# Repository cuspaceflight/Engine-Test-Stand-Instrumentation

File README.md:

# Cambridge University Space Flight Engine Test Stand

This repo contains documents for CUSF engine test stand. The electronics are split across 2 circuit boards:

**Servo + Solenoid Board**  Drives 2 solenoid valves (MPQ6610 half-bridge ICs) and up to 4 servos
**Instrumentation Board** Reads pressure transducers, thermocouples, and a load cell for thrust measurement

A laptop running ground-station software sends commands to the ESP32 on the servo board, and polls the Instrumentation Board to read sensor data

## Board Details

### Servo + Solenoid Board

This board contains the circuits for driving the servos and solenoids. Uses an ESP32 microcontroller (ESP32 S3 DevKit C1). The microcontroller is alos responsible for: 
 - Communication with laptop
 - Driving servos and solenoids
 - Inputs raw data from sensors and sends to laptop

#### Solenoid Section

Each of the solenoid channels uses an **MPS MPQ6610** half-bridge power driver. 

#### Servo Section

4 servos (FeeTech 180 Degrees Digital Servo 7.4V 35kg/cm FT5330M)
 - PWM signal from ESP32

### Instrumentation Board

- Load cell
- 8 Pressure sensors
- 4 thermocouples

## Repository Structure

```
cusf-engine_test_stand/
│
├── hardware/
│   ├── master-board/
│   │   ├── kicad/              # Schematic + PCB project
│   │
│   ├── servo-solenoid-board/
│   │   ├── kicad/
│   │
│   ├── instrumentation-board/
│   │   ├── kicad/
│   │
│   ├── Datasheets
│   │   ├── MPQ6610.pdf
│   │
│
├── Software/
│   ├── servo/
│   ├── solenoid/
│   ├── instrumentation/
│   ├──Laptop software (GUI + logging)
│
└── README.md

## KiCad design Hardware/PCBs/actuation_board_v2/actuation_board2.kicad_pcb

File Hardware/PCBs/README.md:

# CUSF Load Cell Interface Board

## Overview

Signal conditioning board for the PW16A load cell, providing excitation voltage, instrumentation amplification, low-pass filtering, and buffered voltage references for ADC reading.

---

## Connector

| Designator | Description |
|------------|-------------|
| J1 | RS Pro M12 Connector Female, 8W-8C, 5m, PVC, Shield |

---

## Load Cell

| Parameter | Value |
|-----------|-------|
| Model | PW16A |
| Sensitivity | 2 mV/V |
| Excitation Voltage | 10 V |
| Full-scale Output | 20 mV (0.02 V) |

---

## Power Section

### Voltage Regulation & References

| Designator | Part | Description | Package |
|------------|------|-------------|---------|
| U4 | L78L05 | 5V Positive Linear Regulator, 100mA, 30V Max Input | SOIC-8 |
| U2 | REF5010AD | 10V Precision Voltage Reference, 0.1% Accuracy, 10mA, Low Noise | SOIC-8 |
| U5 | REF3033 | 3.3V CMOS Voltage Reference, 50 ppm/°C Max, 50 µA | SOT-23 |

### Op-Amp Buffers

| Designator | Part | Description | Package | Purpose |
|------------|------|-------------|---------|---------|
| U3 | OPA197xD | 36V Precision, Rail-to-Rail I/O, Low Offset Voltage Op-Amp | SOIC-8 | 10V reference buffer |
| U6 | OPA333xxD | 1.8V microPower, CMOS Zero-Drift Op-Amp | SOIC-8 | 3.3V reference buffer |

### Resistors

| Designator | Value | Package |
|------------|-------|---------|
| R2 | 1 Ω | 0805 |
| R3 | 16.2 kΩ | 0805 |
| R4 | 1.8 kΩ | 0805 |

### Capacitors

| Designator | Value | Package |
|------------|-------|---------|
| C3 | 100 nF | 0805 |
| C4 | 100 nF | 0805 |
| C5 | 100 nF | 0805 |
| C6 | 100 nF | 0805 |
| C7 | 10 µF | 0805 |
| C8 | 10 µF | 0805 |
| C9 | 10 µF | 0805 |
| C10 | 1 µF | 0805 |
| C11 | 100 nF | 0805 |
| C12 | 1 µF | 0805 |
| C13 | 100 nF | 0805 |

### Outputs

| Signal | Source | Description |
|--------|--------|-------------|
| VOUT_10V | REF5010AD + OPA197xD buffer | 10V excitation for load cell |
| VREF_0.33V | REF3033 + OPA333xxD buffer | 0.33V reference for ADC |

---

## Analogue Signal Section

### Instrumentation Amplifier

| Designator | Part | Description | Package |
|------------|------|-------------|---------|
| U1 | AD8422 | Single High Performance, Low Power, Rail-to-Rail Precision In-Amp | SOIC-8 |

| Parameter | Value |
|-----------|-------|
| Gain (G) | 150 |
| Gain Resistor (RG) | 133 Ω |
| Formula | RG = 19.8 kΩ / (G − 1) |
| Supply Voltage | +15V (single-supply) |
| Output to ESP | 3.0 V |

### Gain Resistor

| Designator | Value | Package |
|------------|-------|---------|
| RG | 133 Ω | 0805 |

### Low-Pass Filter

| Designator | Value | Package | Notes |
|------------|-------|---------|-------|
| R1 | 5.36 kΩ | 0805 | Series resistor |
| C1 | 10 nF | 0805 | Shunt capacitor |

| Parameter | Value |
|-----------|-------|
| Cut-off Frequency | 2.97 kHz |
| Topology | RC low-pass filter |

### Decoupling Capacitor

| Designator | Value | Package |
|------------|-------|---------|
| C2 | 0.1 µF | 0805 |

### Signals

| Signal | Direction | Description |
|--------|-----------|-------------|
| LC_SIG+ | Input | Load cell differential signal (+) |
| LC_SIG- | Input | Load cell differential signal (−) |
| +15V_Analog | Input | 15V supply for AD8422 |
| V_REF | Input | 0.33V reference for AD8422 output offset |
| ADC_OUT_TO_MIC | Output | Filtered, amplified signal to microcontroller ADC |
| AGND | — | Analogue ground |

---

## Inter-Sheet Connections

| Main Sheet Label | Power Sheet | Analogue Signal Sheet | J1 (M12 Connector) |
|------------------|-------------|----------------------|---------------------|
| VIN_15V | Input | — | — |
| VOUT_10V | ← Output | — | — |
| VREF_0.33V | ← Output | → V_REF | — |
| +10V_EXC | — | — | Pins 1, 8 |
| LC_SIG+ | — | ← Input | Pin (signal) |
| LC_SIG- | — | ← Input | Pin (signal) |
| AGND | ✓ | ✓ | Ground pins |
| ADC_OUT_TO_MIC | — | → Output | — |

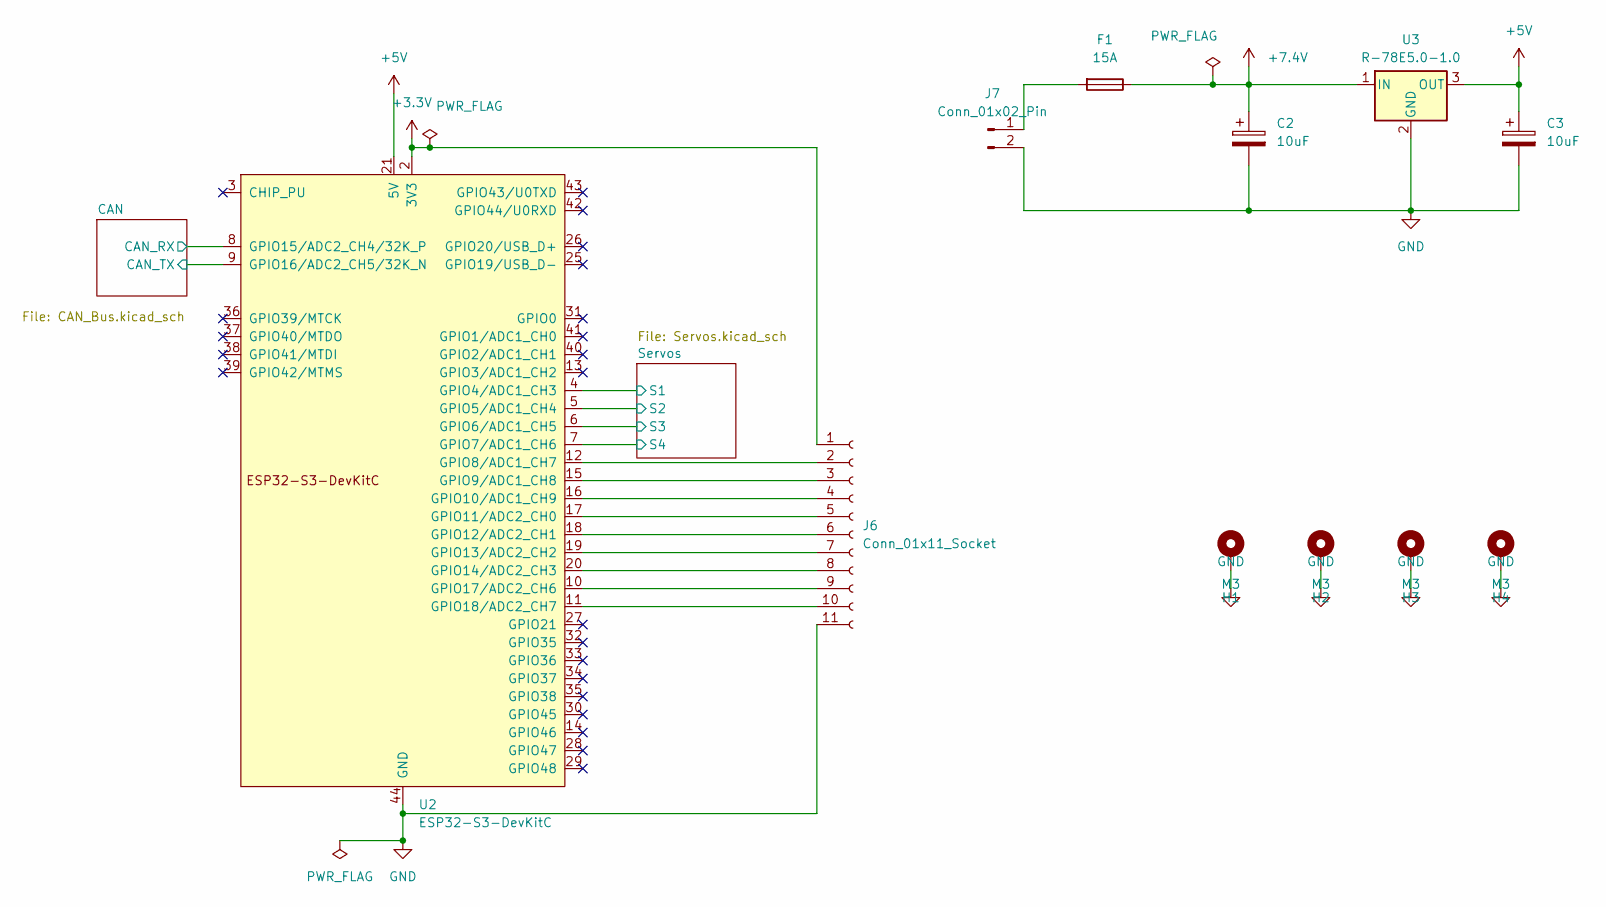
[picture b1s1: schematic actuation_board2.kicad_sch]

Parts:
C2, C3: 10uF; C_0603_1608Metric_Pad1.08x0.95mm_HandSolder
F1: 15A; Fuse_1206_3216Metric_Pad1.42x1.75mm_HandSolder
H1, H2, H3, H4: M3; MountingHole_3.2mm_M3_Pad_Via
J6: Conn_01x11_Socket; PinSocket_1x11_P2.54mm_Vertical
J7: Conn_01x02_Pin; AMASS_XT60PW-M_1x02_P7.20mm_Horizontal
U2: ESP32-S3-DevKitC
U3: R-78E5.0-1.0; Converter_DCDC_RECOM_R-78E-0.5_THT

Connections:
+3.3V: J6.1, U2.1 (3V3), U2.2 (3V3); also elsewhere on the board
+5V: C3.1, U2.21 (5V), U3.3 (OUT)
+7.4V: C2.1, F1.1, U3.1 (IN); also elsewhere on the board
/CAN/CAN_RX: U2.8 (GPIO15/ADC2_CH4/32K_P); also elsewhere on the board
/CAN/CAN_TX: U2.9 (GPIO16/ADC2_CH5/32K_N); also elsewhere on the board
/Servos/S1: U2.4 (GPIO4/ADC1_CH3); also elsewhere on the board
/Servos/S2: U2.5 (GPIO5/ADC1_CH4); also elsewhere on the board
/Servos/S3: U2.6 (GPIO6/ADC1_CH5); also elsewhere on the board
/Servos/S4: U2.7 (GPIO7/ADC1_CH6); also elsewhere on the board
GND: C2.2, C3.2, H1.1, H2.1, H3.1, H4.1, J6.11, J7.2, U2.22 (GND), U2.23 (GND), U2.24 (GND), U2.44 (GND), U3.2 (GND); also elsewhere on the board
unnamed: J6.2, U2.12 (GPIO8/ADC1_CH7)
unnamed: J6.3, U2.15 (GPIO9/ADC1_CH8)
unnamed: J6.4, U2.16 (GPIO10/ADC1_CH9)
unnamed: J6.5, U2.17 (GPIO11/ADC2_CH0)
unnamed: J6.6, U2.18 (GPIO12/ADC2_CH1)
unnamed: J6.7, U2.19 (GPIO13/ADC2_CH2)
unnamed: J6.8, U2.20 (GPIO14/ADC2_CH3)
unnamed: J6.9, U2.10 (GPIO17/ADC2_CH6)
unnamed: J6.10, U2.11 (GPIO18/ADC2_CH7)
unnamed: F1.2, J7.1

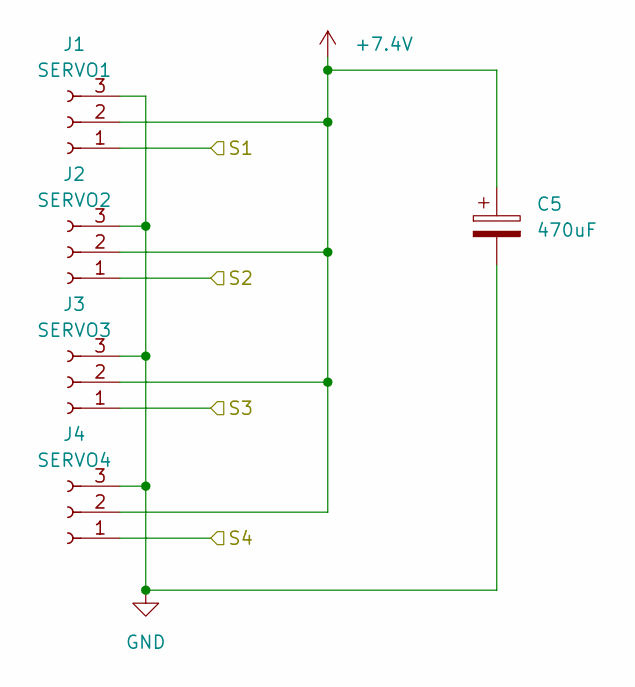
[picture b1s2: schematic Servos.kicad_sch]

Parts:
C5: 470uF; CP_Radial_D10.0mm_P7.50mm
J1: SERVO1; PinHeader_1x03_P2.54mm_Vertical
J2: SERVO2; PinHeader_1x03_P2.54mm_Vertical
J3: SERVO3; PinHeader_1x03_P2.54mm_Vertical
J4: SERVO4; PinHeader_1x03_P2.54mm_Vertical

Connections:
+7.4V: C5.1, J1.2, J2.2, J3.2, J4.2; also elsewhere on the board
/Servos/S1: J1.1; also elsewhere on the board
/Servos/S2: J2.1; also elsewhere on the board
/Servos/S3: J3.1; also elsewhere on the board
/Servos/S4: J4.1; also elsewhere on the board
GND: C5.2, J1.3, J2.3, J3.3, J4.3; also elsewhere on the board

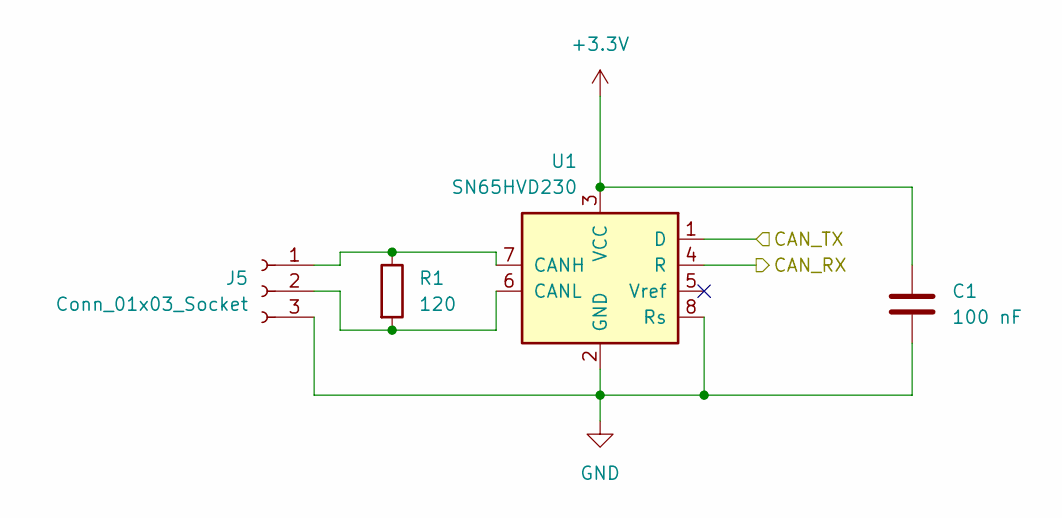
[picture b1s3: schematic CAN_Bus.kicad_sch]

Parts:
C1: 100 nF; C_0603_1608Metric_Pad1.08x0.95mm_HandSolder
J5: Conn_01x03_Socket; PinSocket_1x03_P2.54mm_Vertical
R1: 120; R_0805_2012Metric_Pad1.20x1.40mm_HandSolder
U1: SN65HVD230; SOIC-8_3.9x4.9mm_P1.27mm

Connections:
+3.3V: C1.1, U1.3 (VCC); also elsewhere on the board
/CAN/CAN_RX: U1.4 (R); also elsewhere on the board
/CAN/CAN_TX: U1.1 (D); also elsewhere on the board
GND: C1.2, J5.3, U1.2 (GND), U1.8 (Rs); also elsewhere on the board
unnamed: J5.1, R1.1, U1.7 (CANH)
unnamed: J5.2, R1.2, U1.6 (CANL)

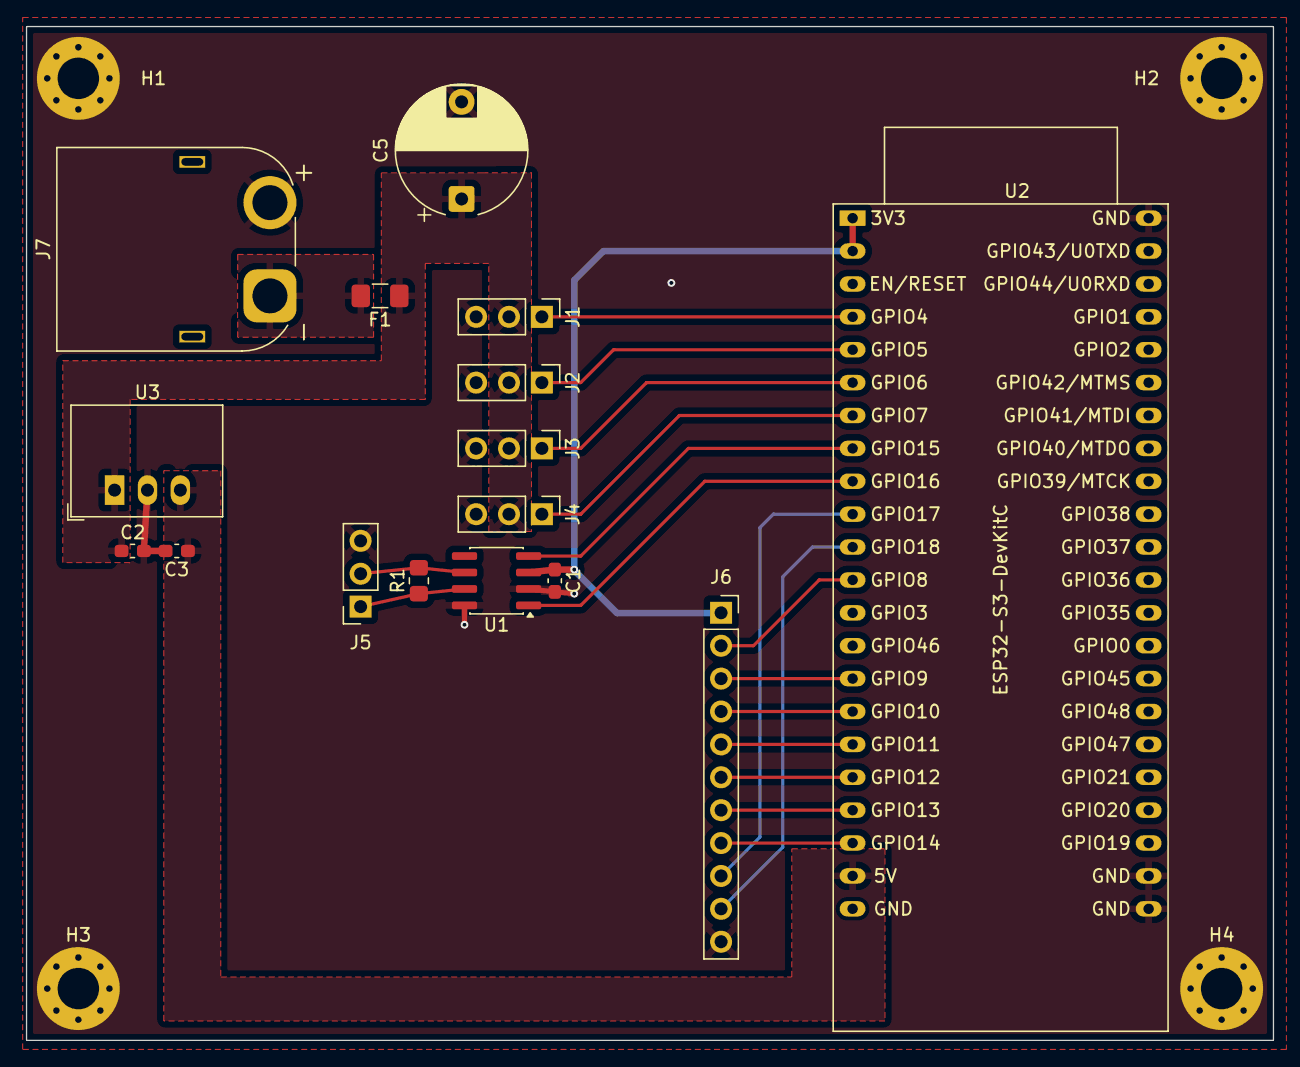
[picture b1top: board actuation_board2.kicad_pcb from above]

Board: 2 copper layers, 96.3 x 78.3 mm, 20 parts (0 on the bottom side), 22 nets.

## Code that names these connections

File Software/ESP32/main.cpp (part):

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    // PWM generator. We configure 4 channels at 50Hz with 14-bit
    // resolution, then attach each to its GPIO pin.
    //
    // Channel 0 → GPIO10 → Servo 1
    // Channel 1 → GPIO11 → Servo 2
    // Channel 2 → GPIO12 → Servo 3
    // Channel 3 → GPIO13 → Servo 4

    int servo_pins[4] = {PIN_SERVO1, PIN_SERVO2, PIN_SERVO3, PIN_SERVO4};

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
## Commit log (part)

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2026-03-08 Add README for CUSF Test Stand actuation board
    Added detailed documentation for the CUSF Test Stand actuation board, including overview, architecture, specifications, safety interlock, GPIO assignments, power distribution, communication protocol,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
2026-03-26 Added Actuation board PCB schematic
2026-03-26 serial_comms..py + explanation of how this code works
2026-03-27 Documentation. GUI Demo (Doesn't fully work)
2026-03-28 bugs
2026-04-02 Works better
2026-04-05 Revise README for clarity and corrections
    Updated README.md to improve clarity and correct typos.
2026-05-10 push
2026-05-10 version1 of esp32 code
2026-05-17 Updated PCB
2026-05-17 updated software
2026-05-24 Add initial load cell schematic design
2026-05-24 Moved load cell files to new folder
2026-06-21 Updated code
2026-06-21 Final schematic
2026-06-21 fixed import error in software
2026-06-27 Finished schematic and PCB
